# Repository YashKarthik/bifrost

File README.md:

USB to DisplayPort dongle

**thing to confirm**:
- if i need a different CC/PD controller for active negatiotion of DP alt mode.
- how HPD signals go back to host.
- caps, esd etc

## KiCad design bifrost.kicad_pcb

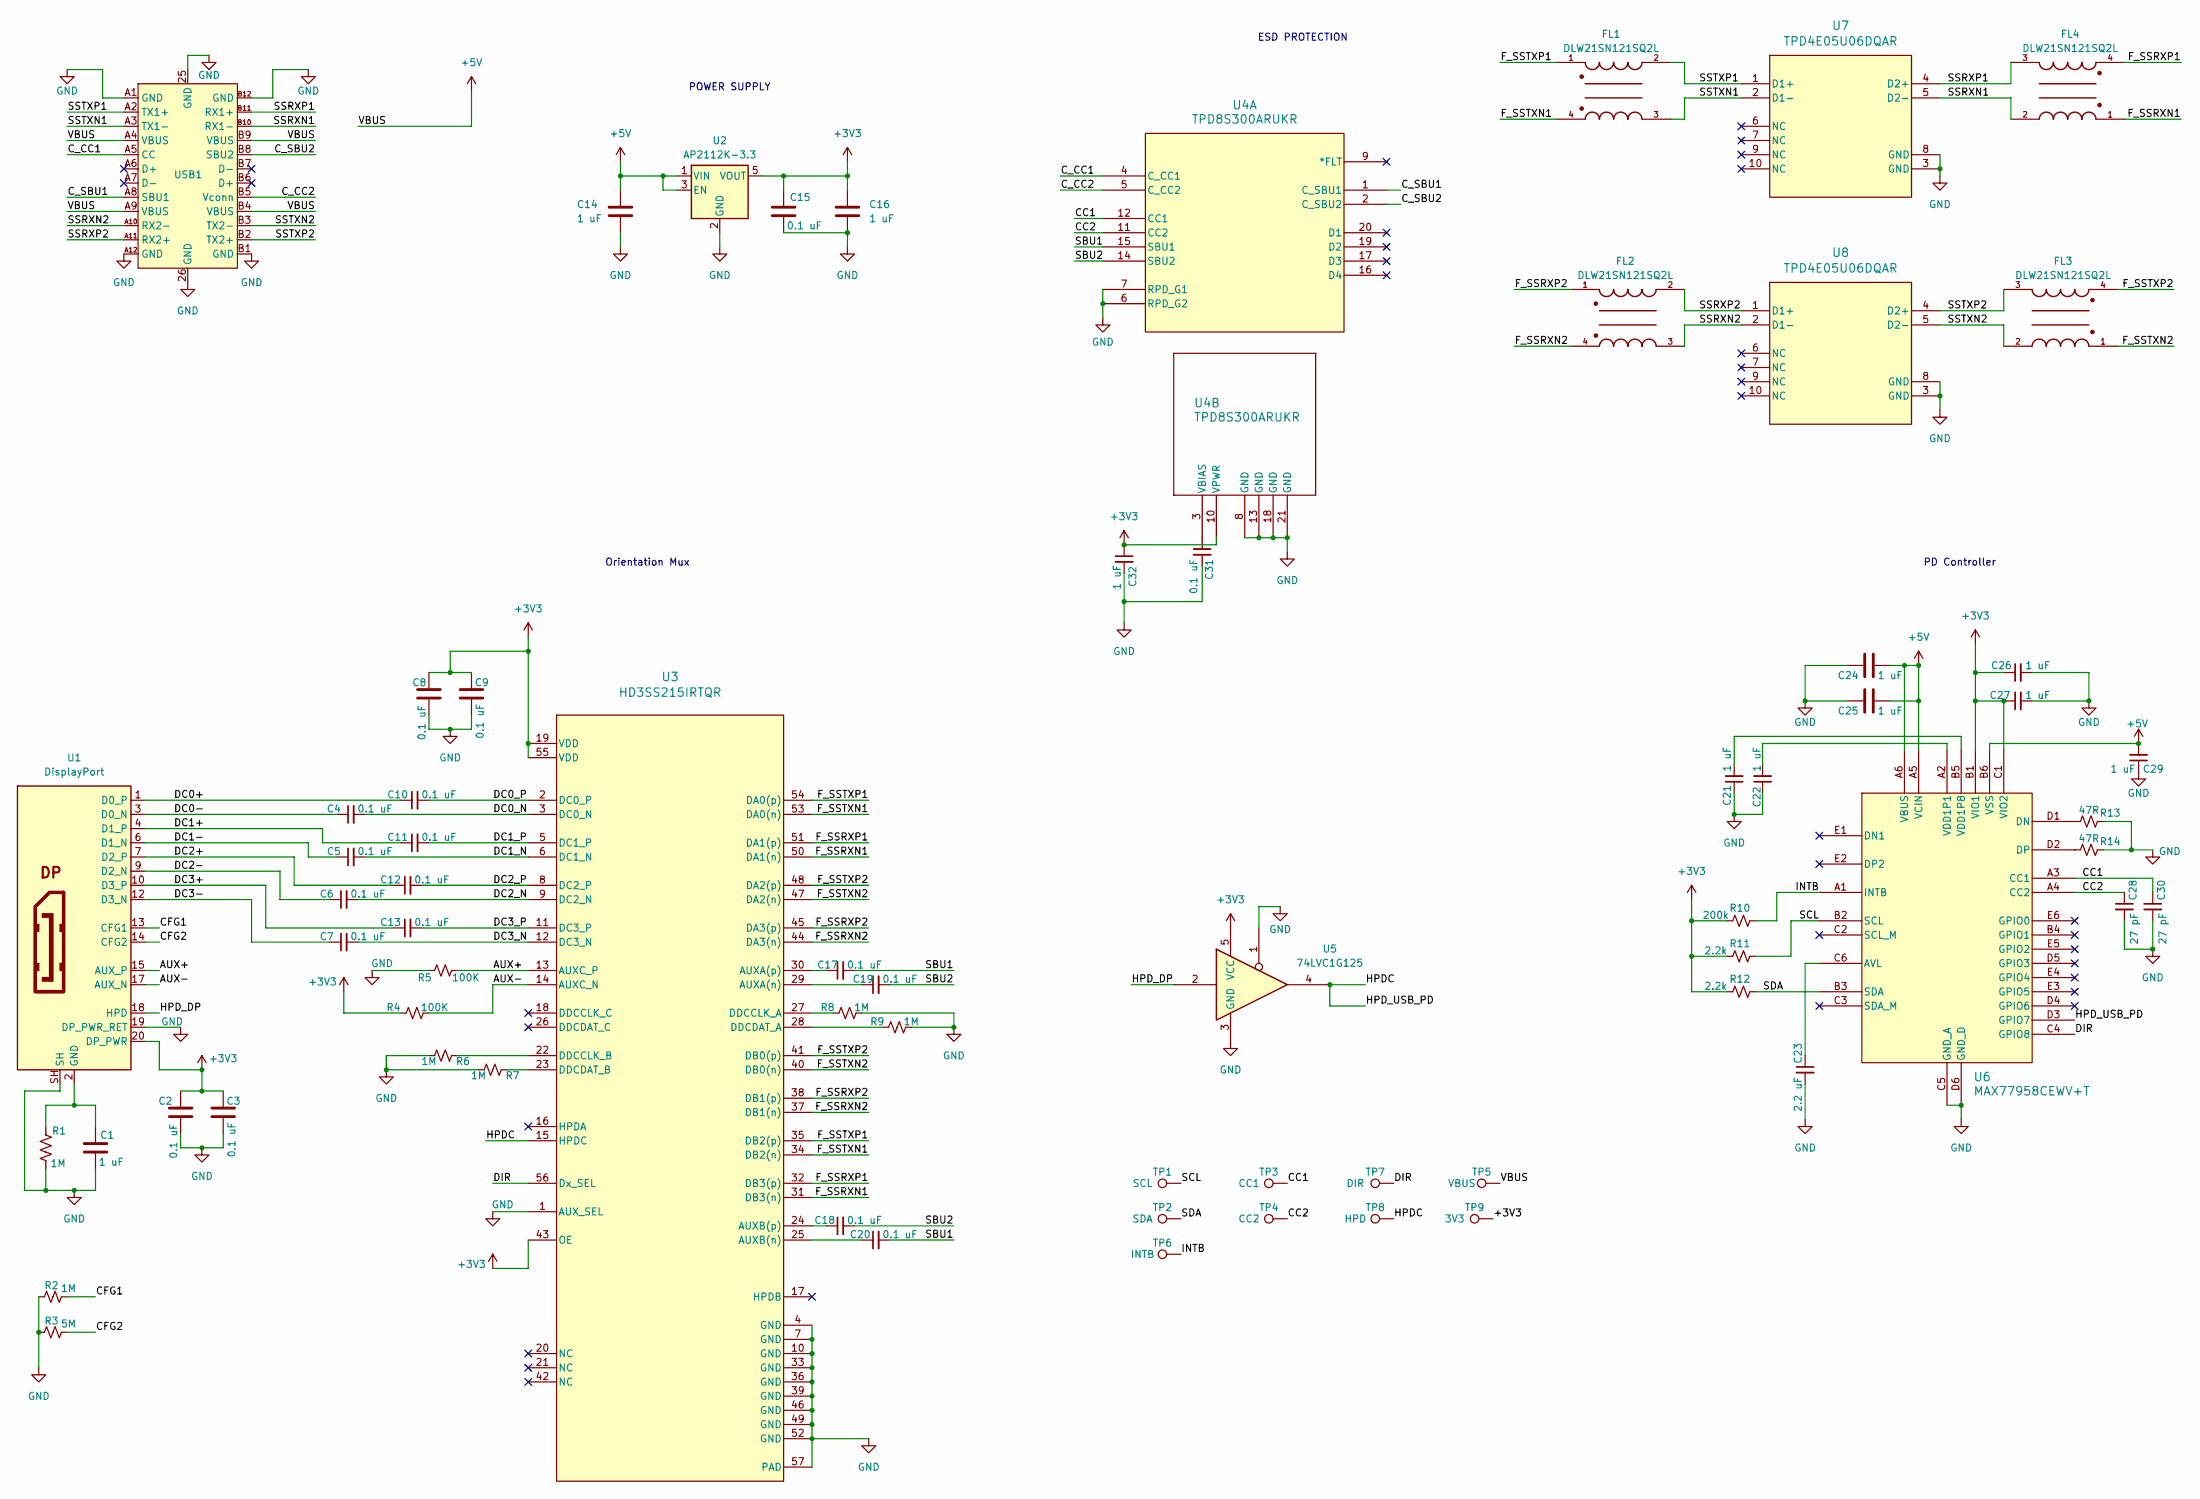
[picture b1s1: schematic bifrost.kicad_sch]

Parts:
C1, C14, C16, C21, C22, C24, C25, C26, C27, C29, C32: 1 uF; C_0603_1608Metric_Pad1.08x0.95mm_HandSolder
C2, C3, C4, C5, C6, C7, C8, C9, C10, C11, C12, C13, C15, C17, C18, C19, C20, C31: 0.1 uF; C_0603_1608Metric_Pad1.08x0.95mm_HandSolder
C23: 2.2 uF; C_0805_2012Metric_Pad1.18x1.45mm_HandSolder
C28, C30: 27 pF; C_0603_1608Metric_Pad1.08x0.95mm_HandSolder
FL1, FL2, FL3, FL4: DLW21SN121SQ2L
R1, R2, R6, R7, R8, R9: 1M; R_0603_1608Metric_Pad0.98x0.95mm_HandSolder
R3: 5M; R_0603_1608Metric_Pad0.98x0.95mm_HandSolder
R4, R5: 100K; R_0603_1608Metric_Pad0.98x0.95mm_HandSolder
R10: 200k; R_0603_1608Metric_Pad0.98x0.95mm_HandSolder
R11, R12: 2.2k; R_0603_1608Metric_Pad0.98x0.95mm_HandSolder
R13, R14: 47R; R_0603_1608Metric_Pad0.98x0.95mm_HandSolder
TP1: SCL; TestPoint_Pad_D3.0mm
TP2: SDA; TestPoint_Pad_D3.0mm
TP3: CC1; TestPoint_Pad_D3.0mm
TP4: CC2; TestPoint_Pad_D3.0mm
TP5: VBUS; TestPoint_Pad_D3.0mm
TP6: INTB; TestPoint_Pad_D3.0mm
TP7: DIR; TestPoint_Pad_D3.0mm
TP8: HPD; TestPoint_Pad_D3.0mm
TP9: 3V3; TestPoint_Pad_D3.0mm
U1: DisplayPort; DISPLAYPORT_FEMALE_XDPF-0205-20S
U2: AP2112K-3.3; SOT-23-5
U3: HD3SS215IRTQR; RTQ0056B
U4: TPD8S300ARUKR; WQFN20_RUK_TEX
U5: 74LVC1G125; SOT-353_SC-70-5_Handsoldering
U6: MAX77958CEWV+T; 21-100339_W302B3&plus_1_ADI
U7, U8: TPD4E05U06DQAR; DQA0010A
USB1: USB-C-SMD_U261-241N-4BS2SS; Manufacturer Part U261-241N-4BS2SS

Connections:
+3V3: C2.1, C3.1, C8.1, C9.1, C15.1, C16.1, C26.1, C27.1, C32.1, R4.1, R10.1, R11.1, R12.1, TP9.1, U1.20 (DP_PWR), U2.5 (VOUT), U3.19 (VDD), U3.43 (OE), U3.55 (VDD), U4.10 (VPWR), U5.5 (VCC), U6.B1 (VIO1), U6.C1 (VIO2)
+5V: C14.1, C24.2, C25.2, C29.2, TP5.1, U2.1 (VIN), U2.3 (EN), U6.A5 (VCIN), U6.A6 (VBUS), U6.B6 (VSS), USB1.A4 (VBUS), USB1.A9 (VBUS), USB1.B4 (VBUS), USB1.B9 (VBUS)
/AUX+: R5.2, U1.15 (AUX_P), U3.13 (AUXC_P)
/AUX-: R4.2, U1.17 (AUX_N), U3.14 (AUXC_N)
/CC1: C30.1, TP3.1, U4.12 (CC1), U6.A3 (CC1)
/CC2: C28.1, TP4.1, U4.11 (CC2), U6.A4 (CC2)
/CFG1: R2.2, U1.13 (CFG1)
/CFG2: R3.2, U1.14 (CFG2)
/C_CC1: U4.4 (C_CC1), USB1.A5 (CC)
/C_CC2: U4.5 (C_CC2), USB1.B5 (Vconn)
/C_SBU1: U4.1 (C_SBU1), USB1.A8 (SBU1)
/C_SBU2: U4.2 (C_SBU2), USB1.B8 (SBU2)
/DC0+: C10.1, U1.1 (D0_P)
/DC0-: C4.1, U1.3 (D0_N)
/DC0_N: C4.2, U3.3 (DC0_N)
/DC0_P: C10.2, U3.2 (DC0_P)
/DC1+: C11.1, U1.4 (D1_P)
/DC1-: C5.1, U1.6 (D1_N)
/DC1_N: C5.2, U3.6 (DC1_N)
/DC1_P: C11.2, U3.5 (DC1_P)
/DC2+: C12.1, U1.7 (D2_P)
/DC2-: C6.1, U1.9 (D2_N)
/DC2_N: C6.2, U3.9 (DC2_N)
/DC2_P: C12.2, U3.8 (DC2_P)
/DC3+: C13.1, U1.10 (D3_P)
/DC3-: C7.1, U1.12 (D3_N)
/DC3_N: C7.2, U3.12 (DC3_N)
/DC3_P: C13.2, U3.11 (DC3_P)
/DIR: TP7.1, U3.56 (Dx_SEL), U6.C4 (GPIO8)
/F_SSRXN1: FL4.1, U3.31 (DB3(n)), U3.50 (DA1(n))
/F_SSRXN2: FL2.4, U3.37 (DB1(n)), U3.44 (DA3(n))
/F_SSRXP1: FL4.4, U3.32 (DB3(p)), U3.51 (DA1(p))
/F_SSRXP2: FL2.1, U3.38 (DB1(p)), U3.45 (DA3(p))
/F_SSTXN1: FL1.4, U3.34 (DB2(n)), U3.53 (DA0(n))
/F_SSTXN2: FL3.1, U3.40 (DB0(n)), U3.47 (DA2(n))
/F_SSTXP1: FL1.1, U3.35 (DB2(p)), U3.54 (DA0(p))
/F_SSTXP2: FL3.4, U3.41 (DB0(p)), U3.48 (DA2(p))
/HPDC: TP8.1, U3.15 (HPDC), U5.4, U6.D3 (GPIO7)
/HPD_DP: U1.18 (HPD), U5.2
/INTB: R10.2, TP6.1, U6.A1 (INTB)
/SBU1: C17.2, C20.2, U4.15 (SBU1)
/SBU2: C18.2, C19.2, U4.14 (SBU2)
/SCL: R11.2, TP1.1, U6.B2 (SCL)
/SDA: R12.2, TP2.1, U6.B3 (SDA)
/SSRXN1: FL4.2, U7.5 (D2-), USB1.B10 (RX1-)
/SSRXN2: FL2.3, U8.2 (D1-), USB1.A10 (RX2-)
/SSRXP1: FL4.3, U7.4 (D2+), USB1.B11 (RX1+)
/SSRXP2: FL2.2, U8.1 (D1+), USB1.A11 (RX2+)
/SSTXN1: FL1.3, U7.2 (D1-), USB1.A3 (TX1-)
/SSTXN2: FL3.2, U8.5 (D2-), USB1.B3 (TX2-)
/SSTXP1: FL1.2, U7.1 (D1+), USB1.A2 (TX1+)
/SSTXP2: FL3.3, U8.4 (D2+), USB1.B2 (TX2+)
GND: C1.2, C2.2, C3.2, C8.2, C9.2, C14.2, C15.2, C16.2, C21.1, C22.1, C23.2, C24.1, C25.1, C26.2, C27.2, C28.2, C29.1, C30.2, C31.2, C32.2, R1.2, R2.1, R3.1, R5.1, R6.2, R7.2, R8.2, R9.2, R13.2, R14.2, U1.19 (DP_PWR_RET), U1.SH, U2.2 (GND), U3.1 (AUX_SEL), U3.4 (GND), U3.7 (GND), U3.10 (GND), U3.33 (GND), U3.36 (GND), U3.39 (GND), U3.46 (GND), U3.49 (GND), U3.52 (GND), U3.57 (PAD), U4.6 (RPD_G2), U4.7 (RPD_G1), U4.8 (GND), U4.13 (GND), U4.18 (GND), U4.21 (GND), U5.1, U5.3 (GND), U6.C5 (GND_A), U6.D6 (GND_D), U7.3 (GND), U7.8 (GND), U8.3 (GND), U8.8 (GND), USB1.25 (GND), USB1.26 (GND), USB1.A1 (GND), USB1.A12 (GND), USB1.B1 (GND), USB1.B12 (GND)
unnamed: C1.1, R1.1, U1.2 (GND), U1.5 (GND), U1.8 (GND), U1.11 (GND), U1.16 (GND)
unnamed: C19.1, U3.29 (AUXA(n))
unnamed: C17.1, U3.30 (AUXA(p))
unnamed: C20.1, U3.25 (AUXB(n))
unnamed: C18.1, U3.24 (AUXB(p))
unnamed: R8.1, U3.27 (DDCCLK_A)
unnamed: R6.1, U3.22 (DDCCLK_B)
unnamed: R9.1, U3.28 (DDCDAT_A)
unnamed: R7.1, U3.23 (DDCDAT_B)
unnamed: C31.1, U4.3 (VBIAS)
unnamed: C23.1, U6.C6 (AVL)
unnamed: R13.1, U6.D1 (DN)
unnamed: R14.1, U6.D2 (DP)
unnamed: C22.2, U6.A2 (VDD1P1)
unnamed: C21.2, U6.B5 (VDD1P8)

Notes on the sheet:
PD Controller
ESD PROTECTION
POWER SUPPLY
Orientation Mux

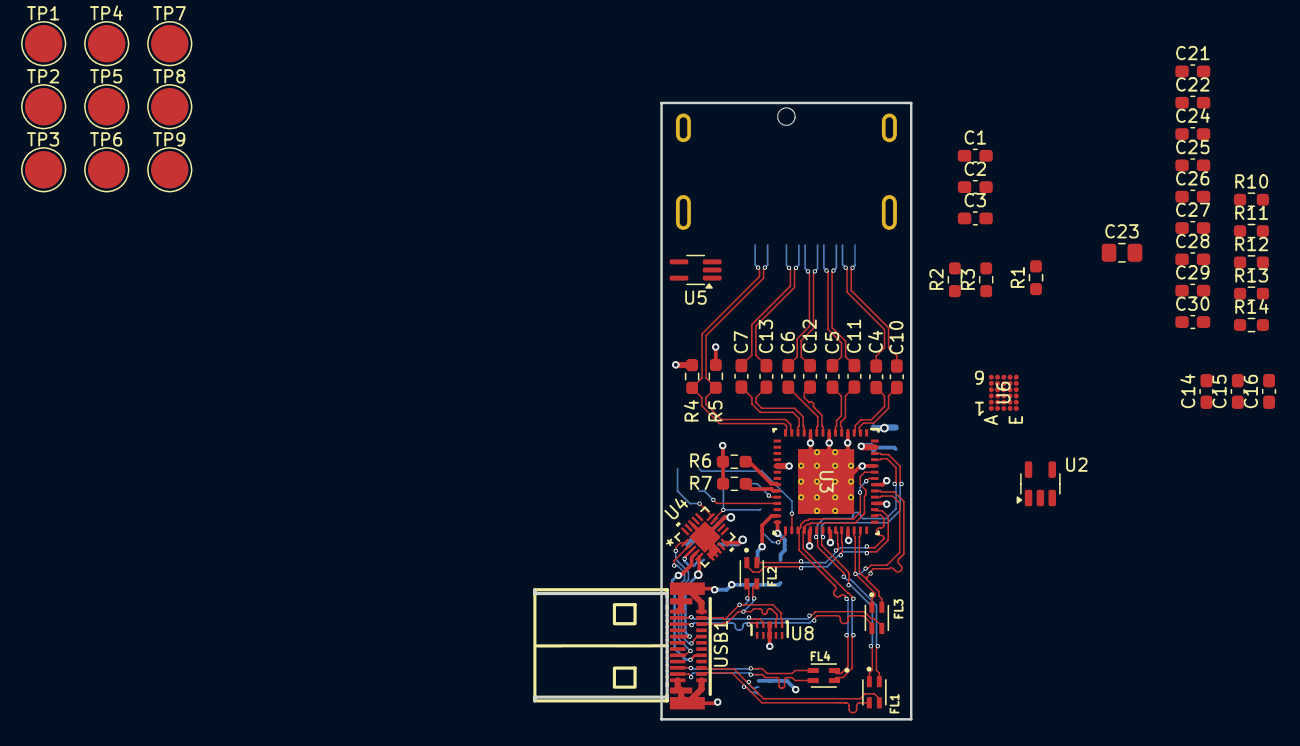
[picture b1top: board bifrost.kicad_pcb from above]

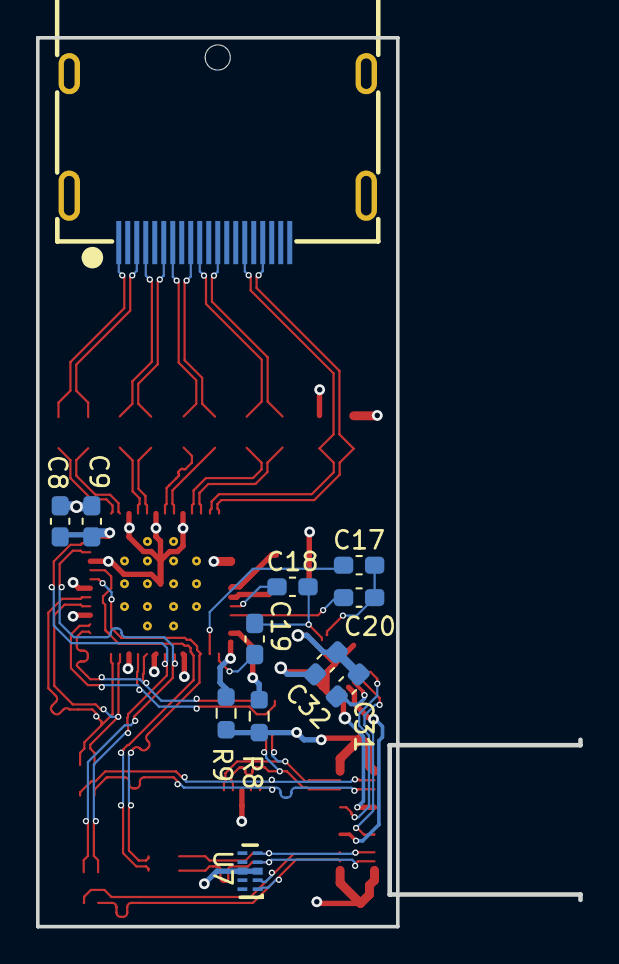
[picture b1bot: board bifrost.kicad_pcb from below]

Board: 4 copper layers, 30.1 x 49.3 mm, 68 parts (12 on the bottom side), 68 nets.

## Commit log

2025-05-18 schematic
2025-05-19 ccaeuntahuntohu anouhe
2025-05-23 schematic done? need to confirm some stuff
2025-05-23 add readme
2025-05-25 schematic done?
2025-05-25 testponits
2025-06-03 thinking of re-layout
